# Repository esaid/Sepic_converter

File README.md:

# Sepic_converter  1A   5V 
LT1372  or CS5171 equivalent

schema  regulateur.sch   et board   regulateur.brd  sous Eagle

input 2.7v --->  28 v     OUT = 5 V  (R2 ,R1 programmable)

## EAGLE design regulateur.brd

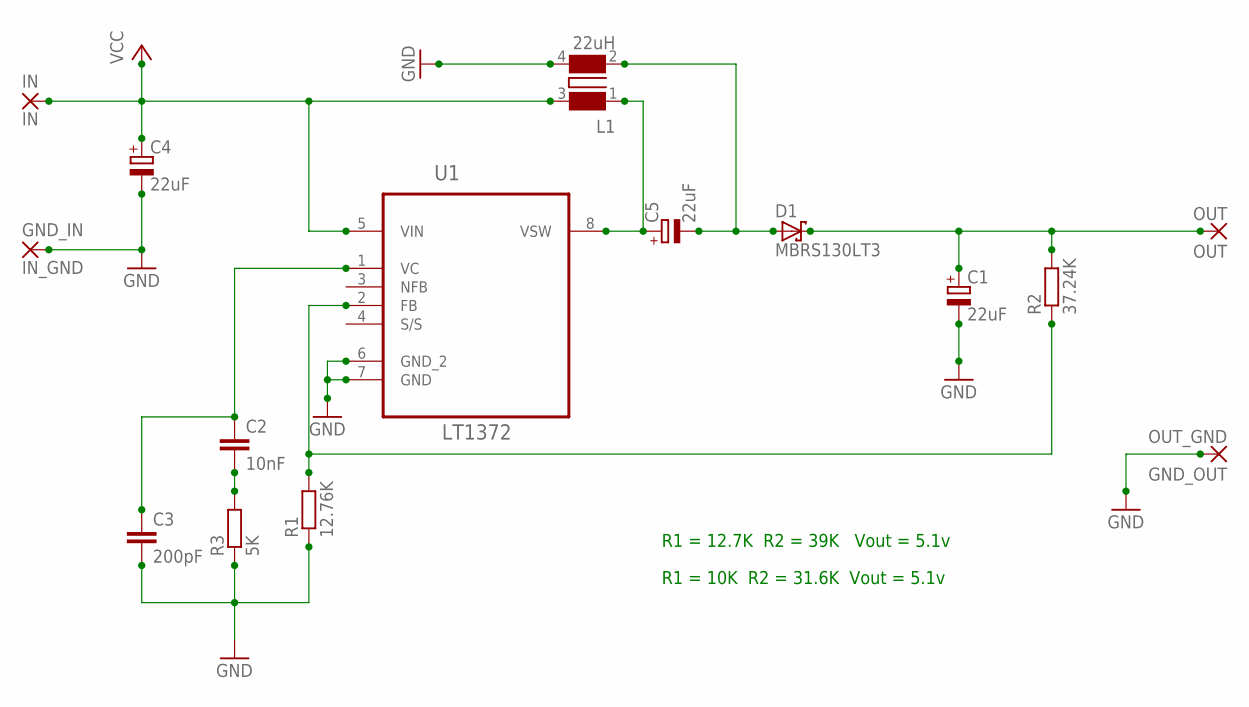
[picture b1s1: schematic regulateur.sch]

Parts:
C1, C4, C5: 22uF; CT7343
C2: 10nF; C1206
C3: 200pF; C1206
D1: MBRS130LT3; SMB
GND_IN: IN_GND; 3,81/1,3
GND_OUT: OUT_GND; 3,81/1,3
IN: IN; 3,81/1,3
L1: 22uH; WE-DD_12XX_CROSSED
OUT: OUT; 3,81/1,3
R1: 12.76K; M1206
R2: 37.24K; M1206
R3: 5K; M1206
U1: LT1372; SOIC127P600X175-8N

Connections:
GND: C1.-, C3.2, C4.-, GND_IN.1, GND_OUT.1, L1.4 (2), R1.1, R3.1, U1.6 (GND_2), U1.7 (GND)
unnamed: C2.2, R3.2
unnamed: C2.1, C3.1, U1.1 (VC)
unnamed: C5.+, L1.1 (3), U1.8 (VSW)
unnamed: C5.-, D1.A, L1.2 (1)
unnamed: C1.+, D1.C, OUT.1, R2.2
unnamed: R1.2, R2.1, U1.2 (FB)
VCC: C4.+, IN.1, L1.3 (4), U1.5 (VIN)

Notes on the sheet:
R1 = 12.7K R2 = 39K Vout = 5.1v
R1 = 10K R2 = 31.6K Vout = 5.1v

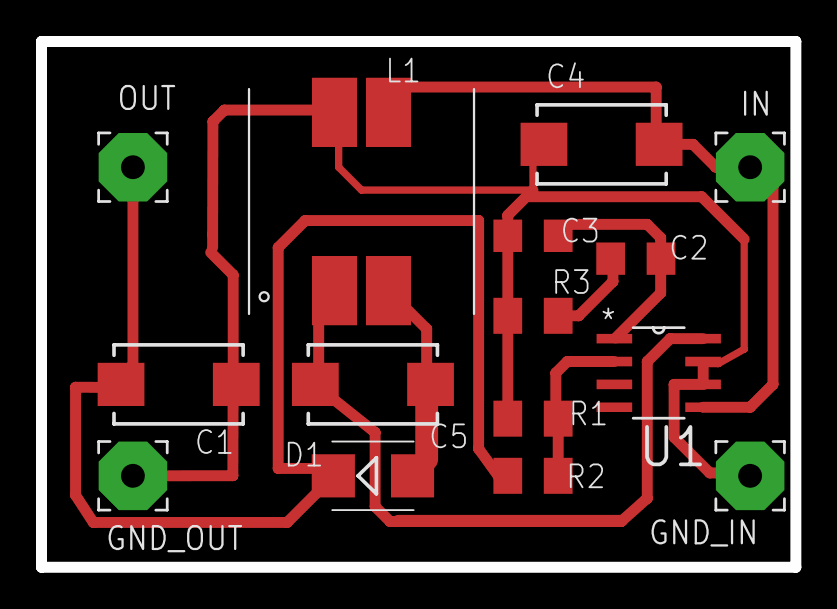
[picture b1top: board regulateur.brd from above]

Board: 2 copper layers, 41.9 x 29.2 mm, 15 parts (0 on the bottom side), 8 nets.

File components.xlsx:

Partlist
Exported | from regulateur | .sch at 19/09/2016 14:19
EAGLE Ver | sion 7.5.0 Copy | right (c) 1988-2015 CadSoft
Assembly | variant:
Part | Value | Device | Package | Library | Sheet
C1 | 22uF | CPOL-EUCT7343 | CT7343 | resistor | 1 | http://fr.farnell.com/avx/tpsd226k035r0200/condensateur-tant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
C2 | 10nF | C-EUC1206 | C1206 | resistor | 1 | http://fr.farnell.com/kemet/c1206c103k5ractu/condensateur-ml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
C3 | 200pF / 220pF | C-EUC1206 | C1206 | resistor | 1 | http://fr.farnell.com/multicomp/mc1206b221k500ct/condensateu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
C4 | 22uF | CPOL-EUCT7343 | CT7343 | resistor | 1 | http://fr.farnell.com/avx/tpsd226k035r0200/condensateur-tant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
C5 | 22uF | CPOL-EUCT7343 | CT7343 | resistor | 1 | http://fr.farnell.com/avx/tpsd226k035r0200/condensateur-tant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
D1 | MBRS130LT3 | MBRS130LT3 | SMB | diode | 1 | http://fr.farnell.com/on-semiconductor/mbrs130lt3g/diode-sch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
GND_IN | IN_GND | 3,81/1,3 | 3,81/1,3 | wirepad | 1
GND_OUT | OUT_GND | 3,81/1,3 | 3,81/1,3 | wirepad | 1
IN | IN | 3,81/1,3 | 3,81/1,3 | wirepad | 1
L1 | 22uH | WE-DD-744871220_1260/1280/1210_CROSSED | WE-DD_12XX_CROSSED | WE-DD | 1 | http://fr.farnell.com/bourns/srf1260a-220m/inductance-pwr-do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
OUT | OUT | 3,81/1,3 | 3,81/1,3 | wirepad | 1
R1 | 12.76K ou 10K | R-EU_M1206 | M1206 | resistor | 1 | http://fr.farnell.com/multicomp/mcwr12x1002ftl/resistance-th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
R2 | 37.24K ou 39K | R-EU_M1206 | M1206 | resistor | 1 | http://fr.farnell.com/welwyn/wcr1206-39kfi/res-couche-epaiss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
R3 | 5K | R-EU_M1206 | M1206 | resistor | 1 | http://fr.farnell.com/vishay/crcw12064k99fkea/res-couche-epa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
U1 | LT1372CS8PBF | LT1372CS8PBF | SOIC127P600X175-8N | LTC_By_element14_Batch_1 | 1 | http://fr.farnell.com/linear-technology/lt1372cs8-pbf/regula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
42635

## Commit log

2016-05-30 simulation LT1362
2016-06-10 Add files via upload
    change package R2 , R1 , R3 , C3
2016-06-20 Add files via upload
    librairie du Sepiv_converter
